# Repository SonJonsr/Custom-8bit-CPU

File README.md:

"# Custom-8bit-CPU" 
"# Custom-8bit-CPU"

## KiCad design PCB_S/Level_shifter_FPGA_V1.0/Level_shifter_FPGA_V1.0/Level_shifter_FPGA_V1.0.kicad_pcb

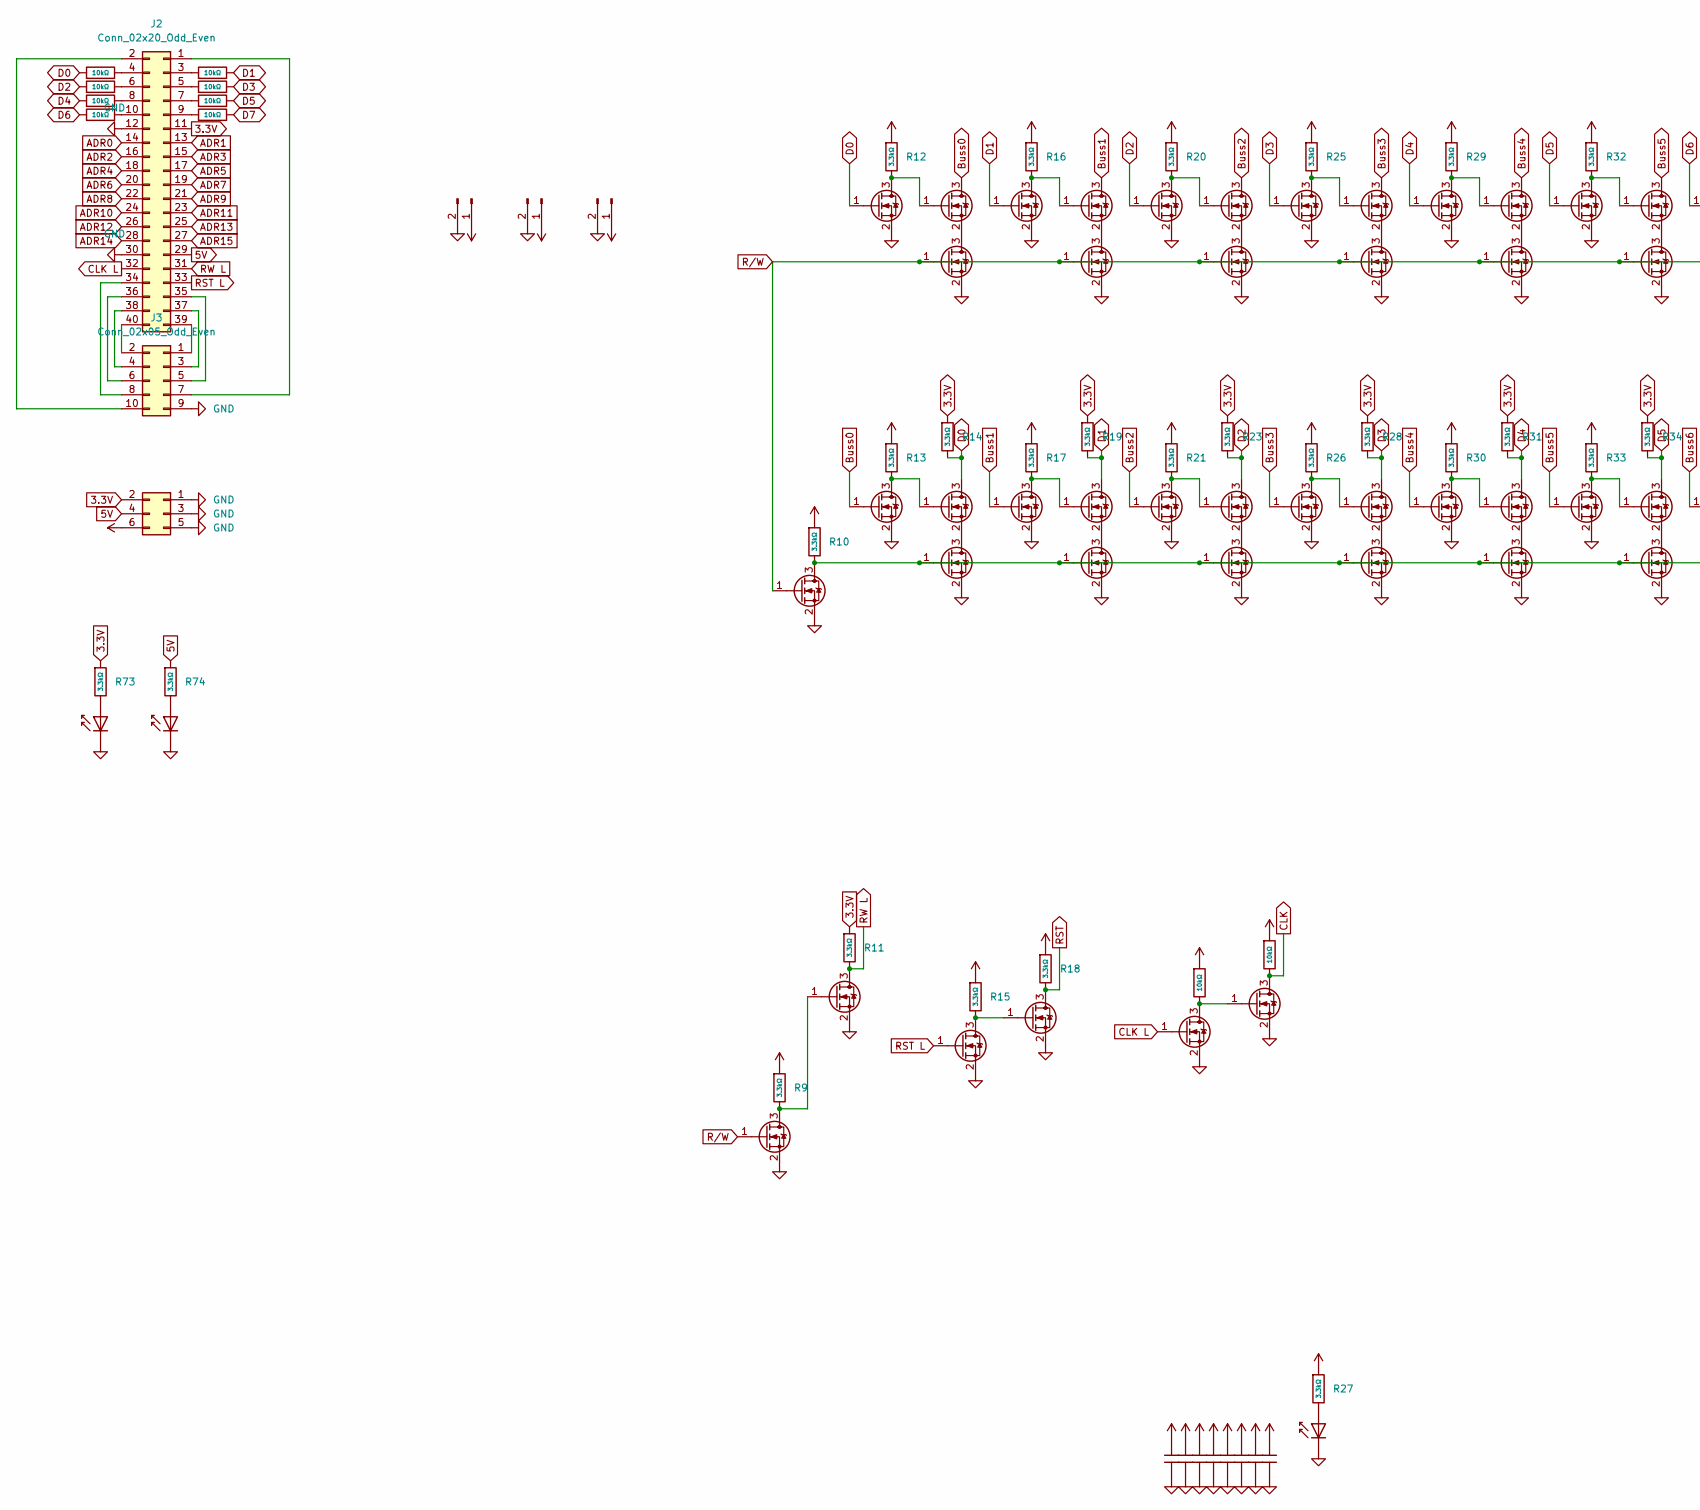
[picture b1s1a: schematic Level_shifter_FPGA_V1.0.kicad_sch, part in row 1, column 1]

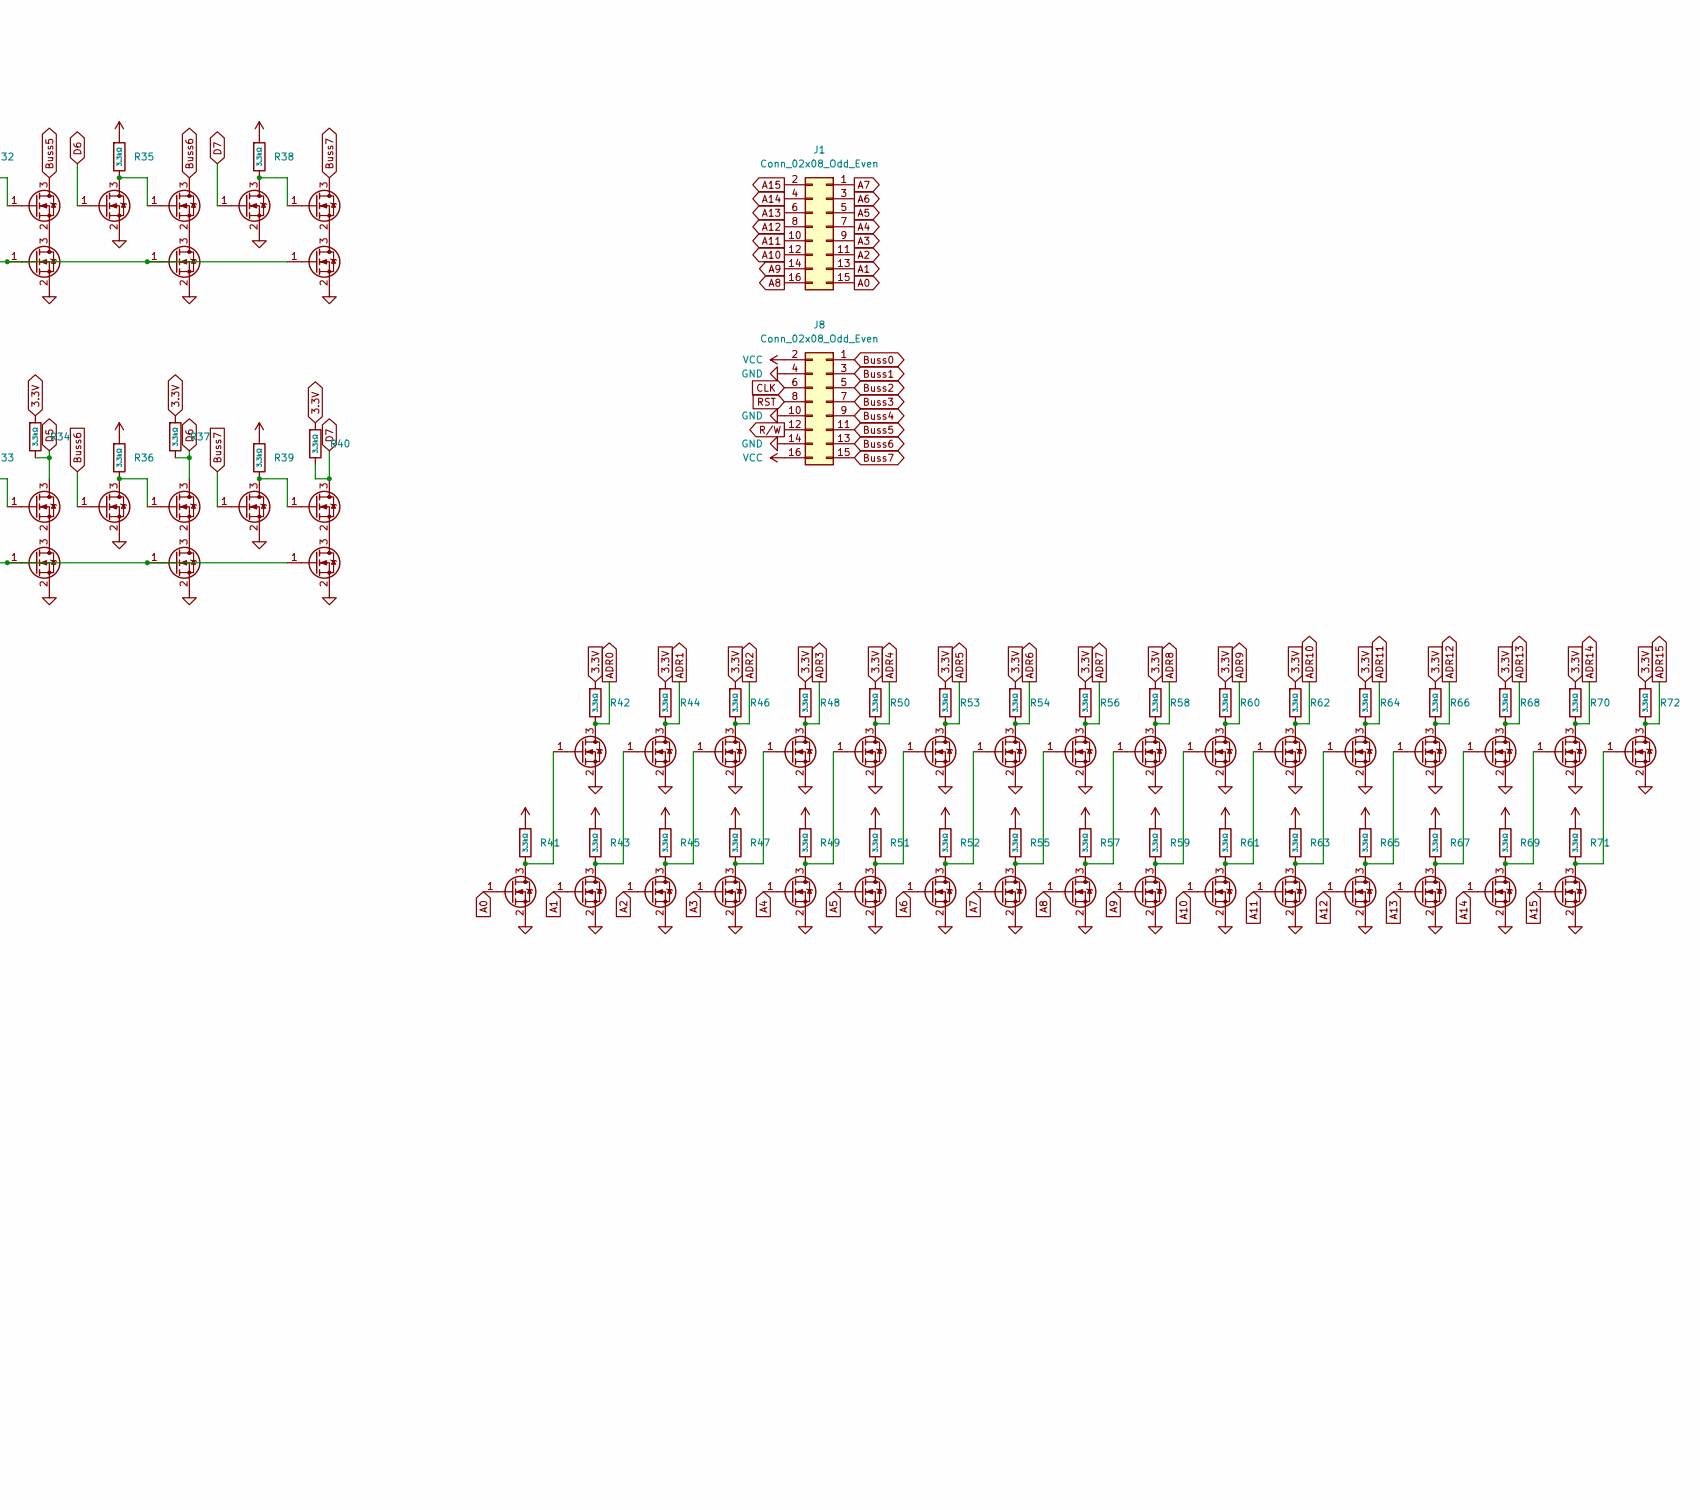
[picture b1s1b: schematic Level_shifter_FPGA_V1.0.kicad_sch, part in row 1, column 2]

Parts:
C1, C2, C3, C4, C5, C6, C7, C8: 22uF; C_0805; Voltage Rated 25V; Tolerance ±20%; Part CL21A226MAQNNNE; LCSC C45783
D1, D2, D3: Red; D_0603; Part KT-0603R; LCSC C2286
J1, J8: Conn_02x08_Odd_Even; PinSocket_2x08_P2.54mm_Vertical
J2: Conn_02x20_Odd_Even; PinSocket_2x20_P2.54mm_Vertical
J3: Conn_02x05_Odd_Even; PinSocket_2x05_P2.54mm_Vertical
J4: Conn_02x03_Odd_Even; PinSocket_2x03_P2.54mm_Vertical
J5, J6, J7: Conn_01x02_Pin; PinSocket_1x02_P2.54mm_Vertical
Q1, Q2, Q3, Q4, Q5, Q6, Q7, Q8, Q9, Q10, Q11, Q12, Q13, Q14, Q15, Q16, Q17, Q18, Q19, Q20, Q21, Q22, Q23, Q24, Q25, Q26, Q27, Q28, Q29, Q30, Q31, Q32, Q33, Q34, Q35, Q36, Q37, Q38, Q39, Q40, Q41, Q42, Q43, Q44, Q45, Q46, Q47, Q48, Q49, Q50, Q51, Q52, Q53, Q54, Q55, Q56, Q57, Q58, Q59, Q60, Q61, Q62, Q63, Q64, Q65, Q66, Q67, Q68, Q69, Q70, Q71, Q72, Q73, Q74, Q75, Q76, Q77, Q78, Q79, Q80, Q81, Q82, Q83, Q84, Q85, Q86, Q87: 2N7002; SOT-23
R1, R2, R3, R4, R5, R6, R7, R8, R22, R24: 10kΩ; R_1206; Overload Voltage (Max) 200V; Tolerance ±1%; Part 1206W4F1002T5E; LCSC C17902
R9, R10, R11, R12, R13, R14, R15, R16, R17, R18, R19, R20, R21, R23, R25, R26, R27, R28, R29, R30, R31, R32, R33, R34, R35, R36, R37, R38, R39, R40, R41, R42, R43, R44, R45, R46, R47, R48, R49, R50, R51, R52, R53, R54, R55, R56, R57, R58, R59, R60, R61, R62, R63, R64, R65, R66, R67, R68, R69, R70, R71, R72, R73, R74: 3.3kΩ; R_0402; Overload Voltage (Max) 50V; Tolerance ±1%; Part 0402WGF3301TCE; LCSC C25890

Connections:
3.3V: J2.11, J4.2, R11.1, R14.1, R19.1, R23.1, R28.1, R31.1, R34.1, R37.1, R40.1, R42.1, R44.1, R46.1, R48.1, R50.1, R53.1, R54.1, R56.1, R58.1, R60.1, R62.1, R64.1, R66.1, R68.1, R70.1, R72.1, R73.1
5V: J2.29, J4.4, R74.1
A0: J1.15, Q56.1 (G)
A1: J1.13, Q58.1 (G)
A2: J1.11, Q60.1 (G)
A3: J1.9, Q62.1 (G)
A4: J1.7, Q64.1 (G)
A5: J1.5, Q66.1 (G)
A6: J1.3, Q68.1 (G)
A7: J1.1, Q70.1 (G)
A8: J1.16, Q72.1 (G)
A9: J1.14, Q74.1 (G)
A10: J1.12, Q76.1 (G)
A11: J1.10, Q78.1 (G)
A12: J1.8, Q80.1 (G)
A13: J1.6, Q82.1 (G)
A14: J1.4, Q84.1 (G)
A15: J1.2, Q86.1 (G)
ADR0: J2.14, Q57.3 (D), R42.2
ADR1: J2.13, Q59.3 (D), R44.2
ADR2: J2.16, Q61.3 (D), R46.2
ADR3: J2.15, Q63.3 (D), R48.2
ADR4: J2.18, Q65.3 (D), R50.2
ADR5: J2.17, Q67.3 (D), R53.2
ADR6: J2.20, Q69.3 (D), R54.2
ADR7: J2.19, Q71.3 (D), R56.2
ADR8: J2.22, Q73.3 (D), R58.2
ADR9: J2.21, Q75.3 (D), R60.2
ADR10: J2.24, Q77.3 (D), R62.2
ADR11: J2.23, Q79.3 (D), R64.2
ADR12: J2.26, Q81.3 (D), R66.2
ADR13: J2.25, Q83.3 (D), R68.2
ADR14: J2.28, Q85.3 (D), R70.2
ADR15: J2.27, Q87.3 (D), R72.2
Buss0: J8.1, Q5.1 (G), Q6.3 (D)
Buss1: J8.3, Q12.1 (G), Q14.3 (D)
Buss2: J8.5, Q19.1 (G), Q21.3 (D)
Buss3: J8.7, Q27.1 (G), Q28.3 (D)
Buss4: J8.9, Q33.1 (G), Q34.3 (D)
Buss5: J8.11, Q39.1 (G), Q40.3 (D)
Buss6: J8.13, Q45.1 (G), Q46.3 (D)
Buss7: J8.15, Q51.1 (G), Q52.3 (D)
CLK: J8.6, Q25.3 (D), R24.2
CLK L: J2.32, Q20.1 (G)
D0: Q4.1 (G), Q8.3 (D), R1.1, R14.2
D1: Q11.1 (G), Q16.3 (D), R2.2, R19.2
D2: Q18.1 (G), Q23.3 (D), R3.1, R23.2
D3: Q26.1 (G), Q30.3 (D), R4.2, R28.2
D4: Q32.1 (G), Q36.3 (D), R5.1, R31.2
D5: Q38.1 (G), Q42.3 (D), R6.2, R34.2
D6: Q44.1 (G), Q48.3 (D), R7.1, R37.2
D7: Q50.1 (G), Q54.3 (D), R8.2, R40.2
GND: C1.2, C2.2, C3.2, C4.2, C5.2, C6.2, C7.2, C8.2, D1.1, D2.1, D3.1, J2.12, J2.30, J3.9, J4.1, J4.3, J4.5, J5.2, J6.2, J7.2, J8.4, J8.10, J8.14, Q1.2 (S), Q2.2 (S), Q3.2 (S), Q4.2 (S), Q5.2 (S), Q7.2 (S), Q9.2 (S), Q10.2 (S), Q11.2 (S), Q12.2 (S), Q13.2 (S), Q15.2 (S), Q17.2 (S), Q18.2 (S), Q19.2 (S), Q20.2 (S), Q22.2 (S), Q24.2 (S), Q25.2 (S), Q26.2 (S), Q27.2 (S), Q29.2 (S), Q31.2 (S), Q32.2 (S), Q33.2 (S), Q35.2 (S), Q37.2 (S), Q38.2 (S), Q39.2 (S), Q41.2 (S), Q43.2 (S), Q44.2 (S), Q45.2 (S), Q47.2 (S), Q49.2 (S), Q50.2 (S), Q51.2 (S), Q53.2 (S), Q55.2 (S), Q56.2 (S), Q57.2 (S), Q58.2 (S), Q59.2 (S), Q60.2 (S), Q61.2 (S), Q62.2 (S), Q63.2 (S), Q64.2 (S), Q65.2 (S), Q66.2 (S), Q67.2 (S), Q68.2 (S), Q69.2 (S), Q70.2 (S), Q71.2 (S), Q72.2 (S), Q73.2 (S), Q74.2 (S), Q75.2 (S), Q76.2 (S), Q77.2 (S), Q78.2 (S), Q79.2 (S), Q80.2 (S), Q81.2 (S), Q82.2 (S), Q83.2 (S), Q84.2 (S), Q85.2 (S), Q86.2 (S), Q87.2 (S)
unnamed: D1.2, R27.2
unnamed: D2.2, R73.2
unnamed: D3.2, R74.2
unnamed: J2.1, J3.7
unnamed: J2.2, J3.10
unnamed: J2.3, R2.1
unnamed: J2.4, R1.2
unnamed: J2.5, R4.1
unnamed: J2.6, R3.2
unnamed: J2.7, R6.1
unnamed: J2.8, R5.2
unnamed: J2.9, R8.1
unnamed: J2.10, R7.2
unnamed: J2.34, J3.8
unnamed: J2.35, J3.5
unnamed: J2.36, J3.6
unnamed: J2.37, J3.3
unnamed: J2.38, J3.4
unnamed: J2.39, J3.1
unnamed: J2.40, J3.2
unnamed: Q1.3 (D), Q3.1 (G), R9.2
unnamed: Q4.3 (D), Q6.1 (G), R12.2
unnamed: Q5.3 (D), Q8.1 (G), R13.2
unnamed: Q6.2 (S), Q7.3 (D)
unnamed: Q8.2 (S), Q9.3 (D)
unnamed: Q10.3 (D), Q13.1 (G), R15.2
unnamed: Q11.3 (D), Q14.1 (G), R16.2
unnamed: Q12.3 (D), Q16.1 (G), R17.2
unnamed: Q14.2 (S), Q15.3 (D)
unnamed: Q16.2 (S), Q17.3 (D)
unnamed: Q2.3 (D), Q9.1 (G), Q17.1 (G), Q24.1 (G), Q31.1 (G), Q37.1 (G), Q43.1 (G), Q49.1 (G), Q55.1 (G), R10.2
unnamed: Q18.3 (D), Q21.1 (G), R20.2
unnamed: Q19.3 (D), Q23.1 (G), R21.2
unnamed: Q20.3 (D), Q25.1 (G), R22.2
unnamed: Q21.2 (S), Q22.3 (D)
unnamed: Q23.2 (S), Q24.3 (D)
unnamed: Q26.3 (D), Q28.1 (G), R25.2
unnamed: Q27.3 (D), Q30.1 (G), R26.2
unnamed: Q28.2 (S), Q29.3 (D)
unnamed: Q30.2 (S), Q31.3 (D)
unnamed: Q32.3 (D), Q34.1 (G), R29.2
unnamed: Q33.3 (D), Q36.1 (G), R30.2
unnamed: Q34.2 (S), Q35.3 (D)
unnamed: Q36.2 (S), Q37.3 (D)
unnamed: Q38.3 (D), Q40.1 (G), R32.2
unnamed: Q39.3 (D), Q42.1 (G), R33.2
unnamed: Q40.2 (S), Q41.3 (D)
unnamed: Q42.2 (S), Q43.3 (D)
unnamed: Q44.3 (D), Q46.1 (G), R35.2
unnamed: Q45.3 (D), Q48.1 (G), R36.2
unnamed: Q46.2 (S), Q47.3 (D)
unnamed: Q48.2 (S), Q49.3 (D)
unnamed: Q50.3 (D), Q52.1 (G), R38.2
unnamed: Q51.3 (D), Q54.1 (G), R39.2
unnamed: Q52.2 (S), Q53.3 (D)
unnamed: Q54.2 (S), Q55.3 (D)
unnamed: Q56.3 (D), Q57.1 (G), R41.2
unnamed: Q58.3 (D), Q59.1 (G), R43.2
unnamed: Q60.3 (D), Q61.1 (G), R45.2
unnamed: Q62.3 (D), Q63.1 (G), R47.2
unnamed: Q64.3 (D), Q65.1 (G), R49.2
unnamed: Q66.3 (D), Q67.1 (G), R51.2
unnamed: Q68.3 (D), Q69.1 (G), R52.2
unnamed: Q70.3 (D), Q71.1 (G), R55.2
unnamed: Q72.3 (D), Q73.1 (G), R57.2
unnamed: Q74.3 (D), Q75.1 (G), R59.2
unnamed: Q76.3 (D), Q77.1 (G), R61.2
unnamed: Q78.3 (D), Q79.1 (G), R63.2
unnamed: Q80.3 (D), Q81.1 (G), R65.2
unnamed: Q82.3 (D), Q83.1 (G), R67.2
unnamed: Q84.3 (D), Q85.1 (G), R69.2
unnamed: Q86.3 (D), Q87.1 (G), R71.2
RST: J8.8, Q13.3 (D), R18.2
RST L: J2.33, Q10.1 (G)
RW L: J2.31, Q3.3 (D), R11.2
R/W: J8.12, Q1.1 (G), Q2.1 (G), Q7.1 (G), Q15.1 (G), Q22.1 (G), Q29.1 (G), Q35.1 (G), Q41.1 (G), Q47.1 (G), Q53.1 (G)
VCC: C1.1, C2.1, C3.1, C4.1, C5.1, C6.1, C7.1, C8.1, J4.6, J5.1, J6.1, J7.1, J8.2, J8.16, R9.1, R10.1, R12.1, R13.1, R15.1, R16.1, R17.1, R18.1, R20.1, R21.1, R22.1, R24.1, R25.1, R26.1, R27.1, R29.1, R30.1, R32.1, R33.1, R35.1, R36.1, R38.1, R39.1, R41.1, R43.1, R45.1, R47.1, R49.1, R51.1, R52.1, R55.1, R57.1, R59.1, R61.1, R63.1, R65.1, R67.1, R69.1, R71.1

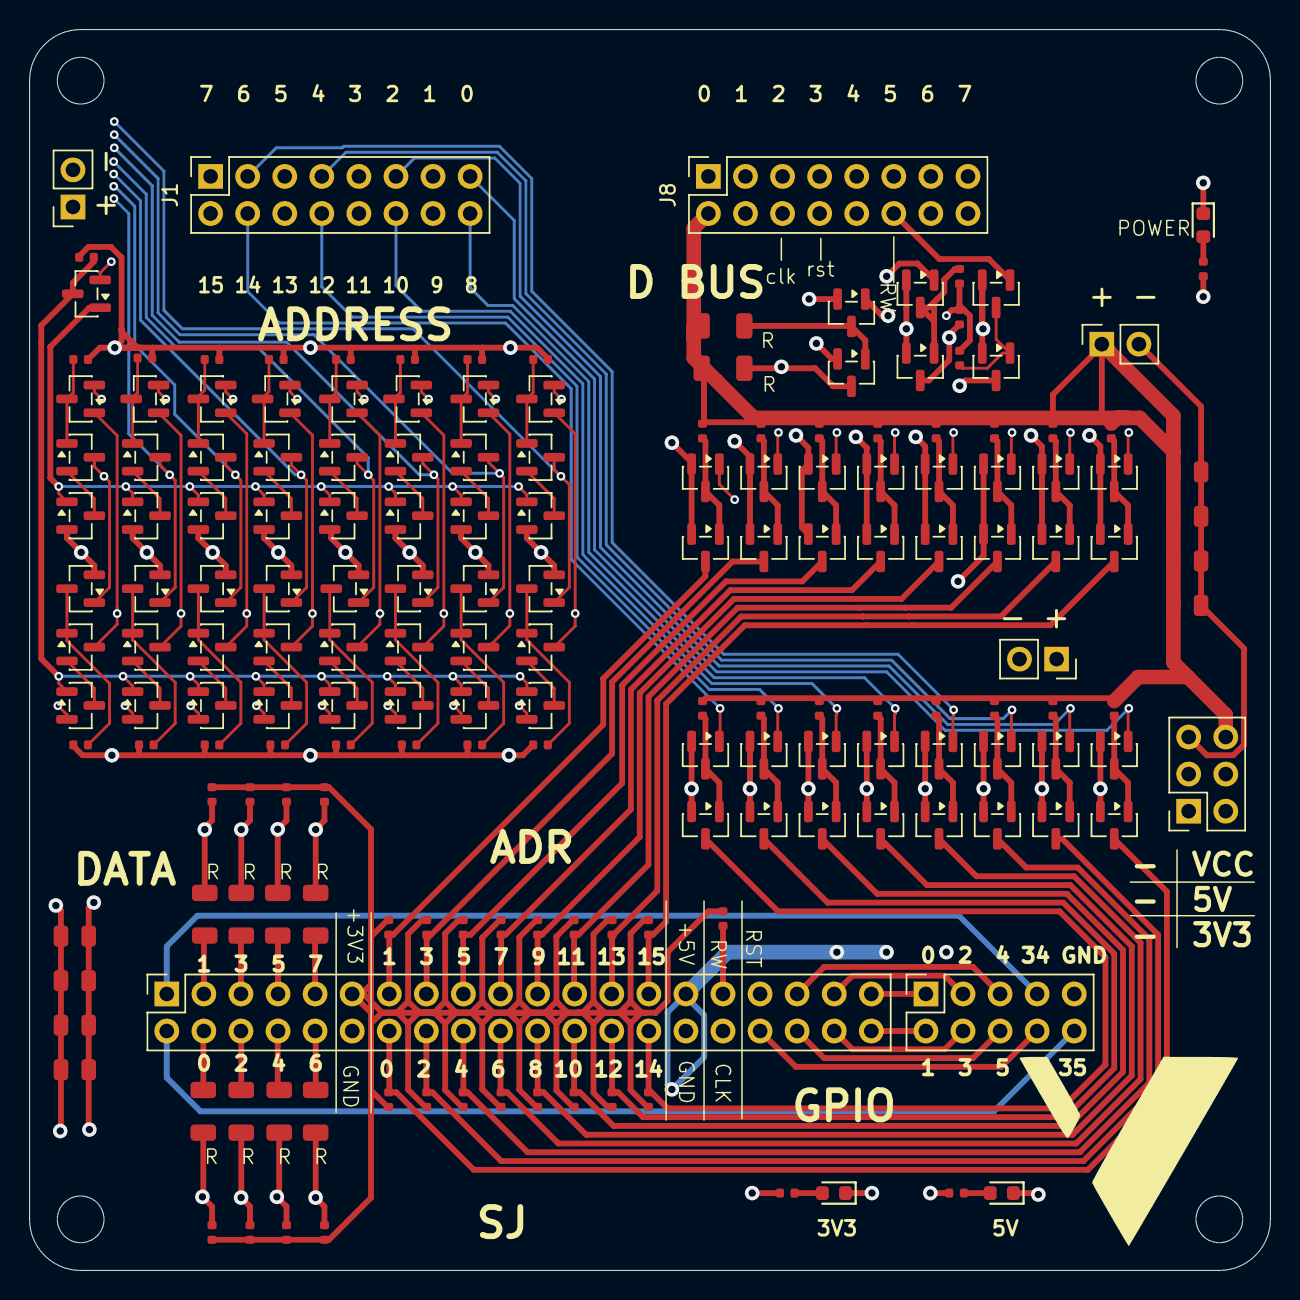
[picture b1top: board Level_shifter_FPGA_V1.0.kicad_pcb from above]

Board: 6 copper layers, 85.0 x 85.0 mm, 184 parts (0 on the bottom side), 130 nets.

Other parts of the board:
H25, H25#2, H25#3, H25#4: MountingHole; MountingHole_3.2mm_M3

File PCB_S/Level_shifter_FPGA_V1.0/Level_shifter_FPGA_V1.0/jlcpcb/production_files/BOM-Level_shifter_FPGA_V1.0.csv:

Comment,Designator,Footprint,LCSC,Quantity
10kΩ,"R1,R2,R22,R24,R3,R4,R5,R6,R7,R8",R_1206,C17902,10
22uF,"C1,C2,C3,C4,C5,C6,C7,C8",C_0805,C45783,8
2N7002,"Q1,Q10,Q11,Q12,Q13,Q14,Q15,Q16,Q17,Q18,Q19,Q2,Q20,Q21,Q22,Q23,Q24,Q25,Q26,Q27,Q28,Q29,Q3,Q30,Q31,Q32,Q33,Q34,Q35,Q36,Q37,Q38,Q39,Q4,Q40,Q41,Q42,Q43,Q44,Q45,Q46,Q47,Q48,Q49,Q5,Q50,Q51,Q52,Q53,Q54,Q55,Q56,Q57,Q58,Q59,Q6,Q60,Q61,Q62,Q63,Q64,Q65,Q66,Q67,Q68,Q69,Q7,Q70,Q71,Q72,Q73,Q74,Q75,Q76,Q77,Q78,Q79,Q8,Q80,Q81,Q82,Q83,Q84,Q85,Q86,Q87,Q9",SOT-23,C8545,87
3.3kΩ,"R10,R11,R12,R13,R14,R15,R16,R17,R18,R19,R20,R21,R23,R25,R26,R27,R28,R29,R30,R31,R32,R33,R34,R35,R36,R37,R38,R39,R40,R41,R42,R43,R44,R45,R46,R47,R48,R49,R50,R51,R52,R53,R54,R55,R56,R57,R58,R59,R60,R61,R62,R63,R64,R65,R66,R67,R68,R69,R70,R71,R72,R73,R74,R9",R_0402,C25890,64
Red,"D1,D2,D3",D_0603,C2286,3
Conn_02x05_Odd_Even,J3,PinSocket_2x05_P2.54mm_Vertical,,1
Conn_02x08_Odd_Even,J8,PinSocket_2x08_P2.54mm_Vertical,,1
Conn_02x08_Odd_Even,J1,PinSocket_2x08_P2.54mm_Vertical,,1
Conn_01x02_Pin,J7,PinSocket_1x02_P2.54mm_Vertical,,1
Conn_01x02_Pin,J6,PinSocket_1x02_P2.54mm_Vertical,,1
Conn_01x02_Pin,J5,PinSocket_1x02_P2.54mm_Vertical,,1
Conn_02x03_Odd_Even,J4,PinSocket_2x03_P2.54mm_Vertical,,1
Conn_02x20_Odd_Even,J2,PinSocket_2x20_P2.54mm_Vertical,,1
